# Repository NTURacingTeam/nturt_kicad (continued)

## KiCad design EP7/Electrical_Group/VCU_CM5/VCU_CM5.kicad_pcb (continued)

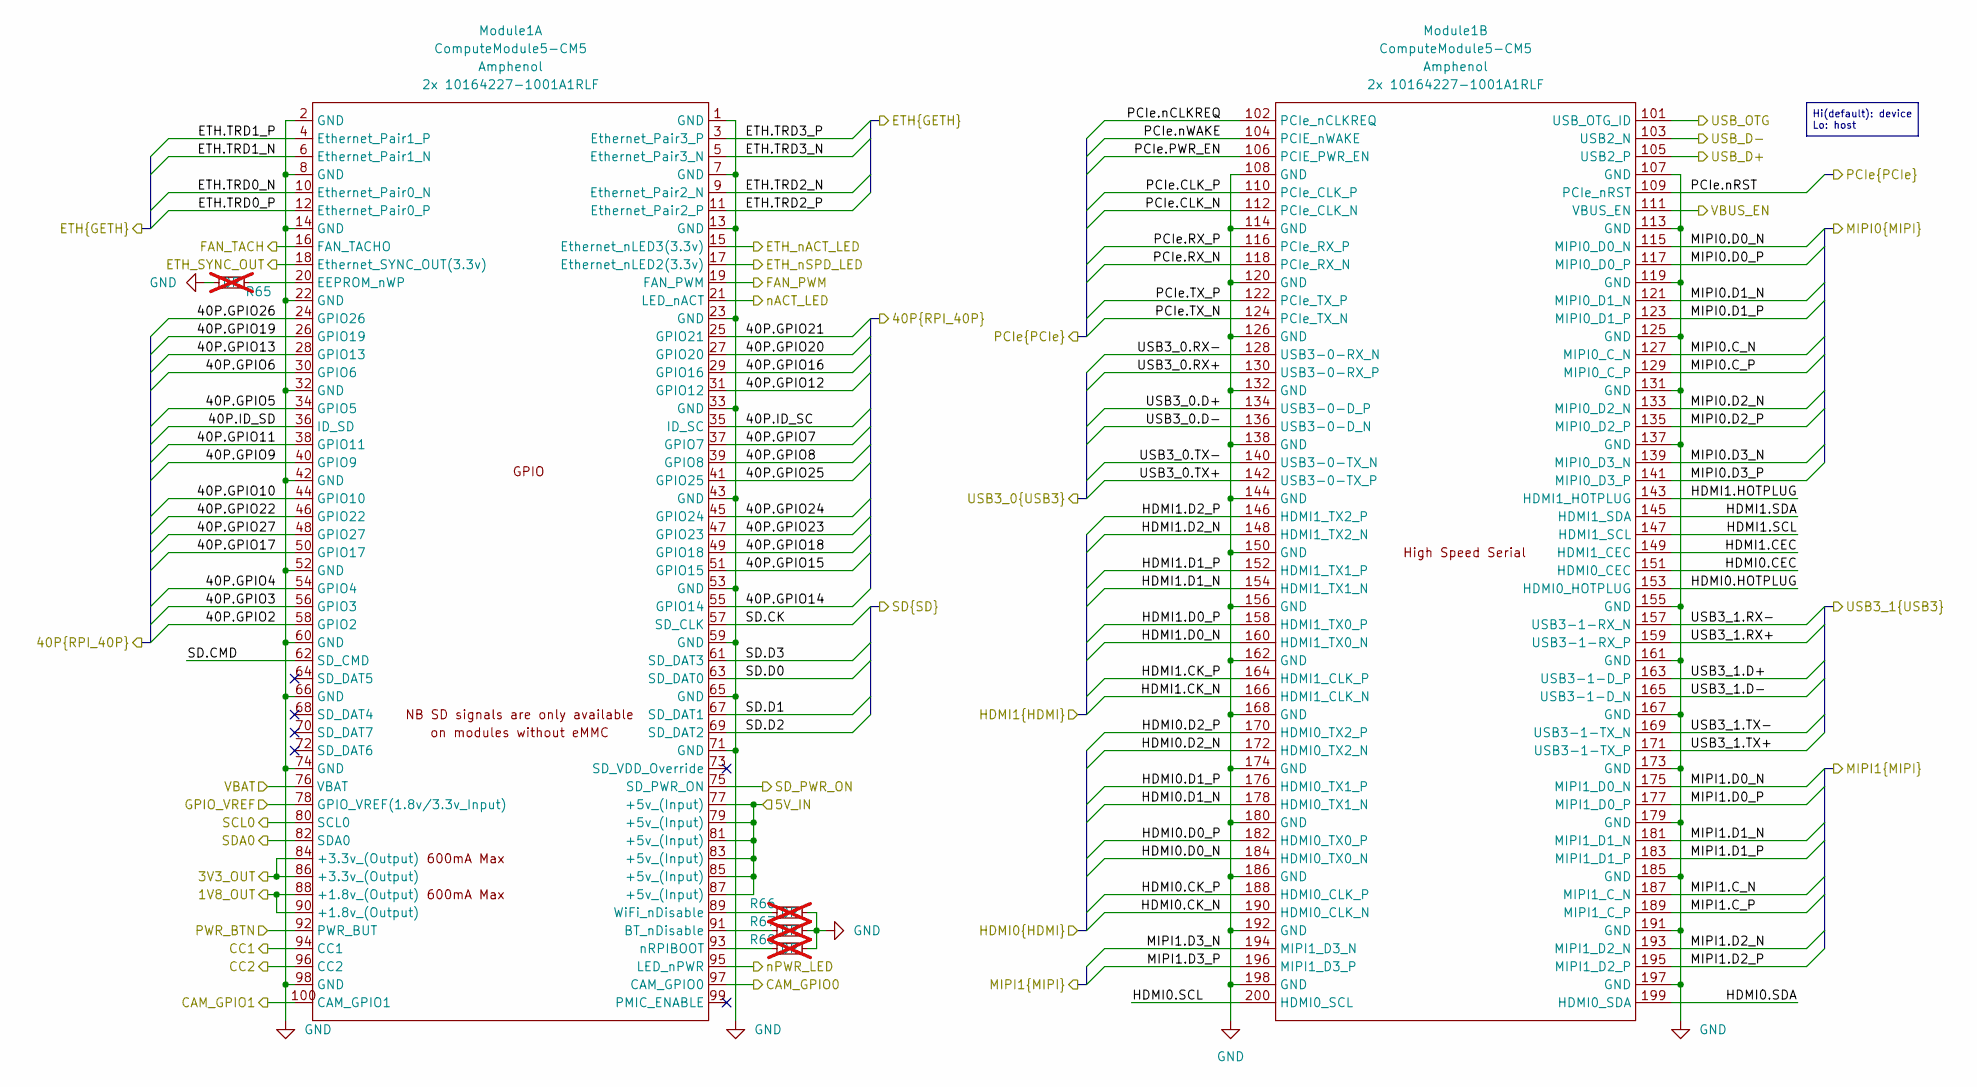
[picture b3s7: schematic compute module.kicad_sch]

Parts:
Module1: ComputeModule5-CM5; Raspberry-Pi-5-Compute-Module
R65, R66, R67, R68: 0R; R_0402_1005Metric; not fitted

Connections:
+1V8_CMOUT: Module1.88 (+1.8v_(Output)), Module1.90 (+1.8v_(Output))
+3V3_CMOUT: Module1.78 (GPIO_VREF(1.8v/3.3v_Input)), Module1.84 (+3.3v_(Output)), Module1.86 (+3.3v_(Output)); also elsewhere on the board
+3V_BAT: Module1.76 (VBAT); also elsewhere on the board
+5V_CM: Module1.77 (+5v_(Input)), Module1.79 (+5v_(Input)), Module1.81 (+5v_(Input)), Module1.83 (+5v_(Input)), Module1.85 (+5v_(Input)), Module1.87 (+5v_(Input))
/USB3_1.D+: Module1.163 (USB3-1-D_P); also elsewhere on the board
/USB3_1.D-: Module1.165 (USB3-1-D_N); also elsewhere on the board
/USB3_1.RX+: Module1.159 (USB3-1-RX_P); also elsewhere on the board
/USB3_1.RX-: Module1.157 (USB3-1-RX_N); also elsewhere on the board
/USB3_1.TX+: Module1.171 (USB3-1-TX_P); also elsewhere on the board
/USB3_1.TX-: Module1.169 (USB3-1-TX_N); also elsewhere on the board
/computer/40P.GPIO2: Module1.58 (GPIO2)
/computer/40P.GPIO3: Module1.56 (GPIO3)
/computer/40P.GPIO4: Module1.54 (GPIO4)
/computer/40P.GPIO5: Module1.34 (GPIO5)
/computer/40P.GPIO6: Module1.30 (GPIO6)
/computer/40P.GPIO7: Module1.37 (GPIO7)
/computer/40P.GPIO8: Module1.39 (GPIO8)
/computer/40P.GPIO9: Module1.40 (GPIO9)
/computer/40P.GPIO10: Module1.44 (GPIO10)
/computer/40P.GPIO11: Module1.38 (GPIO11)
/computer/40P.GPIO12: Module1.31 (GPIO12)
/computer/40P.GPIO13: Module1.28 (GPIO13); also elsewhere on the board
/computer/40P.GPIO14: Module1.55 (GPIO14)
/computer/40P.GPIO15: Module1.51 (GPIO15)
/computer/40P.GPIO16: Module1.29 (GPIO16)
/computer/40P.GPIO17: Module1.50 (GPIO17); also elsewhere on the board
/computer/40P.GPIO18: Module1.49 (GPIO18); also elsewhere on the board
/computer/40P.GPIO19: Module1.26 (GPIO19); also elsewhere on the board
/computer/40P.GPIO20: Module1.27 (GPIO20); also elsewhere on the board
/computer/40P.GPIO21: Module1.25 (GPIO21); also elsewhere on the board
/computer/40P.GPIO22: Module1.46 (GPIO22); also elsewhere on the board
/computer/40P.GPIO23: Module1.47 (GPIO23)
/computer/40P.GPIO24: Module1.45 (GPIO24)
/computer/40P.GPIO25: Module1.41 (GPIO25)
/computer/40P.GPIO26: Module1.24 (GPIO26)
/computer/40P.GPIO27: Module1.48 (GPIO27)
/computer/40P.ID_SC: Module1.35 (ID_SC); also elsewhere on the board
/computer/40P.ID_SD: Module1.36 (ID_SD); also elsewhere on the board
/computer/MIPI0.C_N: Module1.127 (MIPI0_C_N); also elsewhere on the board
/computer/MIPI0.C_P: Module1.129 (MIPI0_C_P); also elsewhere on the board
/computer/MIPI0.D0_N: Module1.115 (MIPI0_D0_N); also elsewhere on the board
/computer/MIPI0.D0_P: Module1.117 (MIPI0_D0_P); also elsewhere on the board
/computer/MIPI0.D1_N: Module1.121 (MIPI0_D1_N); also elsewhere on the board
/computer/MIPI0.D1_P: Module1.123 (MIPI0_D1_P); also elsewhere on the board
/computer/MIPI0.D2_N: Module1.133 (MIPI0_D2_N); also elsewhere on the board
/computer/MIPI0.D2_P: Module1.135 (MIPI0_D2_P); also elsewhere on the board
/computer/MIPI0.D3_N: Module1.139 (MIPI0_D3_N); also elsewhere on the board
/computer/MIPI0.D3_P: Module1.141 (MIPI0_D3_P); also elsewhere on the board
/computer/MIPI0.GPIO0: Module1.97 (CAM_GPIO0); also elsewhere on the board
/computer/MIPI0.GPIO1: Module1.100 (CAM_GPIO1); also elsewhere on the board
/computer/MIPI0.SCL: Module1.80 (SCL0); also elsewhere on the board
/computer/MIPI0.SDA: Module1.82 (SDA0); also elsewhere on the board
/computer/PCIe.CLK_N: Module1.112 (PCIe_CLK_N)
/computer/PCIe.CLK_P: Module1.110 (PCIe_CLK_P)
/computer/PCIe.PWR_EN: Module1.106 (PCIE_PWR_EN)
/computer/PCIe.RX_N: Module1.118 (PCIe_RX_N)
/computer/PCIe.RX_P: Module1.116 (PCIe_RX_P)
/computer/PCIe.TX_N: Module1.124 (PCIe_TX_N)
/computer/PCIe.TX_P: Module1.122 (PCIe_TX_P)
/computer/PCIe.nCLKREQ: Module1.102 (PCIe_nCLKREQ)
/computer/PCIe.nRST: Module1.109 (PCIe_nRST)
/computer/PCIe.nWAKE: Module1.104 (PCIE_nWAKE)
/computer/SD.CK: Module1.57 (SD_CLK); also elsewhere on the board
/computer/SD.CMD: Module1.62 (SD_CMD); also elsewhere on the board
/computer/SD.D0: Module1.63 (SD_DAT0); also elsewhere on the board
/computer/SD.D1: Module1.67 (SD_DAT1); also elsewhere on the board
/computer/SD.D2: Module1.69 (SD_DAT2); also elsewhere on the board
/computer/SD.D3: Module1.61 (SD_DAT3); also elsewhere on the board
/computer/SD_PWR_ON: Module1.75 (SD_PWR_ON); also elsewhere on the board
/computer/USB3_0.D+: Module1.134 (USB3-0-D_P); also elsewhere on the board
/computer/USB3_0.D-: Module1.136 (USB3-0-D_N); also elsewhere on the board
/computer/USB3_0.RX+: Module1.130 (USB3-0-RX_P)
/computer/USB3_0.RX-: Module1.128 (USB3-0-RX_N)
/computer/USB3_0.TX+: Module1.142 (USB3-0-TX_P)
/computer/USB3_0.TX-: Module1.140 (USB3-0-TX_N)
/computer/compute module/CC1: Module1.94 (CC1)
/computer/compute module/CC2: Module1.96 (CC2)
/computer/compute module/ETH.TRD0_N: Module1.10 (Ethernet_Pair0_N)
/computer/compute module/ETH.TRD0_P: Module1.12 (Ethernet_Pair0_P)
/computer/compute module/ETH.TRD1_N: Module1.6 (Ethernet_Pair1_N)
/computer/compute module/ETH.TRD1_P: Module1.4 (Ethernet_Pair1_P)
/computer/compute module/ETH.TRD2_N: Module1.9 (Ethernet_Pair2_N)
/computer/compute module/ETH.TRD2_P: Module1.11 (Ethernet_Pair2_P)
/computer/compute module/ETH.TRD3_N: Module1.5 (Ethernet_Pair3_N)
/computer/compute module/ETH.TRD3_P: Module1.3 (Ethernet_Pair3_P)
/computer/compute module/ETH_SYNC_OUT: Module1.18 (Ethernet_SYNC_OUT(3.3v))
/computer/compute module/ETH_nACT_LED: Module1.15 (Ethernet_nLED3(3.3v))
/computer/compute module/ETH_nSPD_LED: Module1.17 (Ethernet_nLED2(3.3v))
/computer/compute module/FAN_PWM: Module1.19 (FAN_PWM); also elsewhere on the board
/computer/compute module/FAN_TACH: Module1.16 (FAN_TACHO); also elsewhere on the board
/computer/compute module/HDMI0.CEC: Module1.151 (HDMI0_CEC)
/computer/compute module/HDMI0.CK_N: Module1.190 (HDMI0_CLK_N)
/computer/compute module/HDMI0.CK_P: Module1.188 (HDMI0_CLK_P)
/computer/compute module/HDMI0.D0_N: Module1.184 (HDMI0_TX0_N)
/computer/compute module/HDMI0.D0_P: Module1.182 (HDMI0_TX0_P)
/computer/compute module/HDMI0.D1_N: Module1.178 (HDMI0_TX1_N)
/computer/compute module/HDMI0.D1_P: Module1.176 (HDMI0_TX1_P)
/computer/compute module/HDMI0.D2_N: Module1.172 (HDMI0_TX2_N)
/computer/compute module/HDMI0.D2_P: Module1.170 (HDMI0_TX2_P)
/computer/compute module/HDMI0.HOTPLUG: Module1.153 (HDMI0_HOTPLUG)
/computer/compute module/HDMI0.SCL: Module1.200 (HDMI0_SCL)
/computer/compute module/HDMI0.SDA: Module1.199 (HDMI0_SDA)
/computer/compute module/HDMI1.CEC: Module1.149 (HDMI1_CEC)
/computer/compute module/HDMI1.CK_N: Module1.166 (HDMI1_CLK_N)
/computer/compute module/HDMI1.CK_P: Module1.164 (HDMI1_CLK_P)
/computer/compute module/HDMI1.D0_N: Module1.160 (HDMI1_TX0_N)
/computer/compute module/HDMI1.D0_P: Module1.158 (HDMI1_TX0_P)
/computer/compute module/HDMI1.D1_N: Module1.154 (HDMI1_TX1_N)
/computer/compute module/HDMI1.D1_P: Module1.152 (HDMI1_TX1_P)
/computer/compute module/HDMI1.D2_N: Module1.148 (HDMI1_TX2_N)
/computer/compute module/HDMI1.D2_P: Module1.146 (HDMI1_TX2_P)
/computer/compute module/HDMI1.HOTPLUG: Module1.143 (HDMI1_HOTPLUG)
/computer/compute module/HDMI1.SCL: Module1.147 (HDMI1_SCL)
/computer/compute module/HDMI1.SDA: Module1.145 (HDMI1_SDA)
/computer/compute module/MIPI1.C_N: Module1.187 (MIPI1_C_N); also elsewhere on the board
/computer/compute module/MIPI1.C_P: Module1.189 (MIPI1_C_P); also elsewhere on the board
/computer/compute module/MIPI1.D0_N: Module1.175 (MIPI1_D0_N); also elsewhere on the board
/computer/compute module/MIPI1.D0_P: Module1.177 (MIPI1_D0_P); also elsewhere on the board
/computer/compute module/MIPI1.D1_N: Module1.181 (MIPI1_D1_N); also elsewhere on the board
/computer/compute module/MIPI1.D1_P: Module1.183 (MIPI1_D1_P); also elsewhere on the board
/computer/compute module/MIPI1.D2_N: Module1.193 (MIPI1_D2_N)
/computer/compute module/MIPI1.D2_P: Module1.195 (MIPI1_D2_P)
/computer/compute module/MIPI1.D3_N: Module1.194 (MIPI1_D3_N)
/computer/compute module/MIPI1.D3_P: Module1.196 (MIPI1_D3_P)
/computer/compute module/PWR_BTN: Module1.92 (PWR_BUT); also elsewhere on the board
/computer/compute module/USB_D+: Module1.105 (USB2_P)
/computer/compute module/USB_D-: Module1.103 (USB2_N)
/computer/compute module/VBUS_EN: Module1.111 (VBUS_EN)
/computer/compute module/nACT_LED: Module1.21 (LED_nACT); also elsewhere on the board
/computer/compute module/nPWR_LED: Module1.95 (LED_nPWR)
GND: Module1.1 (GND), Module1.2 (GND), Module1.7 (GND), Module1.8 (GND), Module1.13 (GND), Module1.14 (GND), Module1.22 (GND), Module1.23 (GND), Module1.32 (GND), Module1.33 (GND), Module1.42 (GND), Module1.43 (GND), Module1.52 (GND), Module1.53 (GND), Module1.59 (GND), Module1.60 (GND), Module1.65 (GND), Module1.66 (GND), Module1.71 (GND), Module1.74 (GND), Module1.98 (GND), Module1.101 (USB_OTG_ID), Module1.107 (GND), Module1.108 (GND), Module1.113 (GND), Module1.114 (GND), Module1.119 (GND), Module1.120 (GND), Module1.125 (GND), Module1.126 (GND), Module1.131 (GND), Module1.132 (GND), Module1.137 (GND), Module1.138 (GND), Module1.144 (GND), Module1.150 (GND), Module1.155 (GND), Module1.156 (GND), Module1.161 (GND), Module1.162 (GND), Module1.167 (GND), Module1.168 (GND), Module1.173 (GND), Module1.174 (GND), Module1.179 (GND), Module1.180 (GND), Module1.185 (GND), Module1.186 (GND), Module1.191 (GND), Module1.192 (GND), Module1.197 (GND), Module1.198 (GND), R65.1, R66.2, R67.2, R68.2; also elsewhere on the board
unnamed: Module1.91 (BT_nDisable), R67.1
unnamed: Module1.20 (EEPROM_nWP), R65.2
unnamed: Module1.89 (WiFi_nDisable), R66.1
unnamed: Module1.93 (nRPIBOOT), R68.1

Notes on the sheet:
Hi(default): device Lo: host

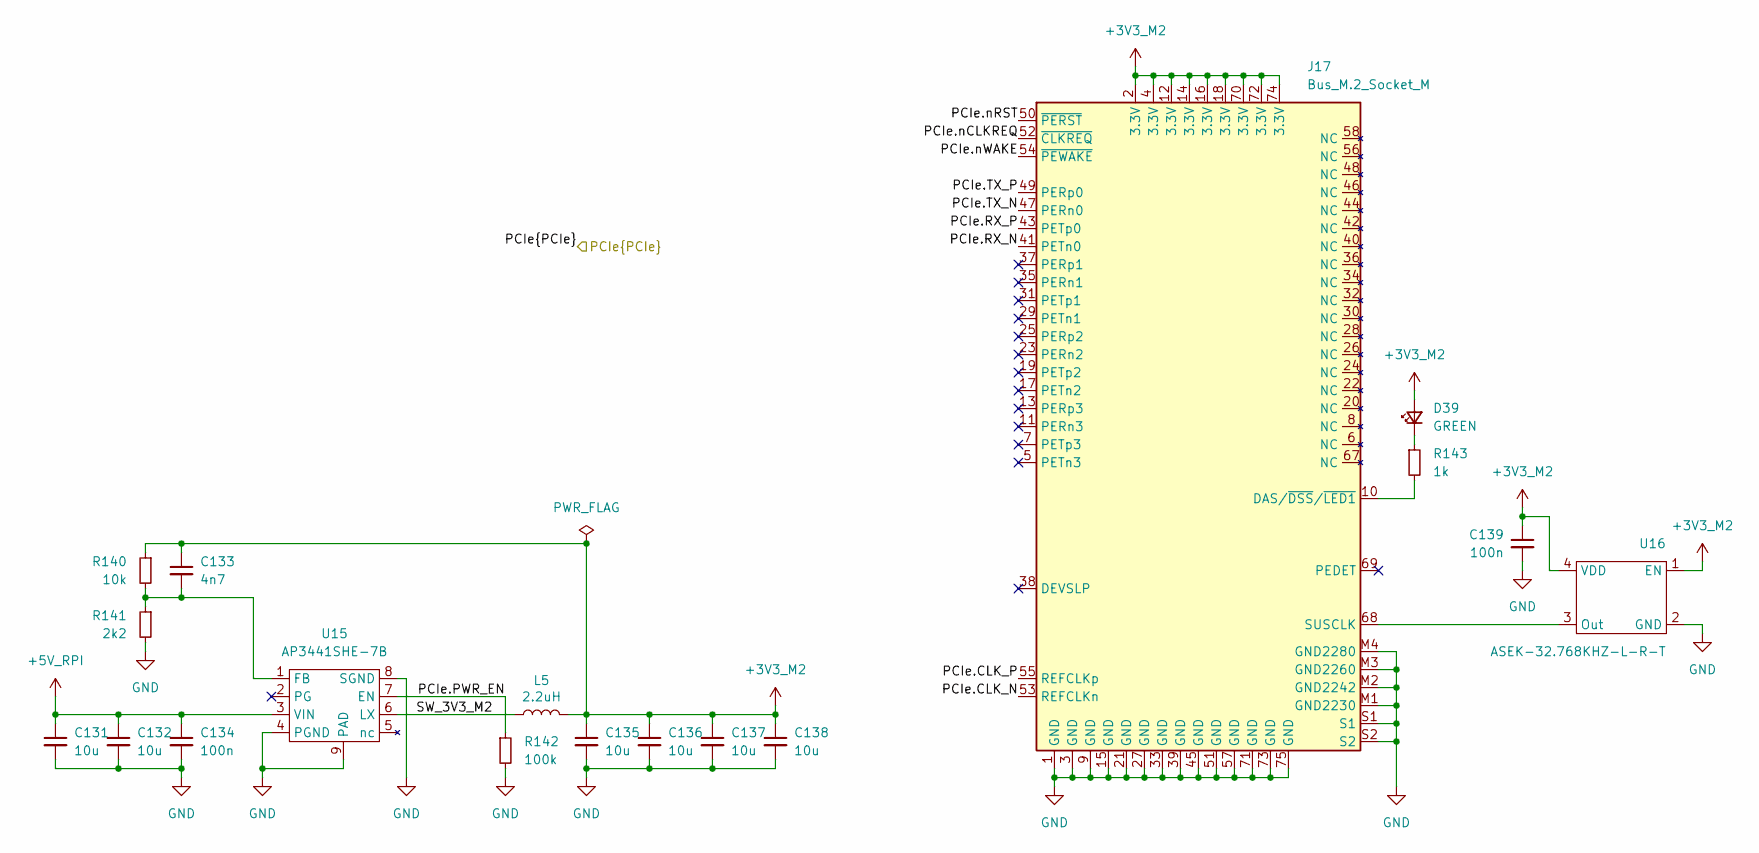
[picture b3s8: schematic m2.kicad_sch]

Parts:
C131, C132, C135, C136, C137, C138: 10u; C_0603_1608Metric
C133: 4n7; C_0402_1005Metric
C134, C139: 100n; C_0402_1005Metric
D39: GREEN; LED_0603_1608Metric
J17: Bus_M.2_Socket_M; M.2 M Key socket; Part Description M.2 M Key connector
L5: 2.2uH; L_Bourns_SRP5030CC; Part Description Inductor, SMT, 2520, 2u2, IRMS=7A, ISAT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
R140: 10k; R_0402_1005Metric
R141: 2k2; R_0402_1005Metric
R142: 100k; R_0402_1005Metric
R143: 1k; R_0402_1005Metric
U15: AP3441SHE-7B; DFN-8-1EP_2x2mm_P0.5mm_EP1.05x1.75mm
U16: ASEK-32.768KHZ-L-R-T; Crystal_SMD_3225-4Pin_3.2x2.5mm; Part Description 32KHz Xtal oscilator

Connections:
unnamed: C131.1, C132.1, C134.1, U15.3 (VIN)
unnamed: C131.2, C132.2, C134.2, C135.2, C136.2, C137.2, C138.2, C139.2, J17.1 (GND), J17.3 (GND), J17.9 (GND), J17.15 (GND), J17.21 (GND), J17.27 (GND), J17.33 (GND), J17.39 (GND), J17.45 (GND), J17.51 (GND), J17.57 (GND), J17.71 (GND), J17.73 (GND), J17.75 (GND), J17.M1 (GND2230), J17.M2 (GND2242), J17.M3 (GND2260), J17.M4 (GND2280), J17.S1, J17.S2, R141.2, R142.2, U15.4 (PGND), U15.8 (SGND), U15.9 (PAD), U16.2 (GND)
unnamed: C133.1, C135.1, C136.1, C137.1, C138.1, C139.1, D39.2 (A), J17.2 (3.3V), J17.4 (3.3V), J17.12 (3.3V), J17.14 (3.3V), J17.16 (3.3V), J17.18 (3.3V), J17.70 (3.3V), J17.72 (3.3V), J17.74 (3.3V), L5.2, R140.1, U16.1 (EN), U16.4 (VDD)
unnamed: C133.2, R140.2, R141.1, U15.1 (FB)
unnamed: D39.1 (K), R143.1
unnamed: J17.10 (DAS/~DSS/~LED1), R143.2
unnamed: J17.68 (SUSCLK), U16.3 (Out)
unnamed: L5.1, U15.6 (LX)
unnamed: R142.1, U15.7 (EN)

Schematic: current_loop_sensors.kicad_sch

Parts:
J11: Conn_01x30_Socket; Amphenol_F32Q-1A7x1-11030_1x30-1MP_P0.5mm_Horizontal
R69, R70, R71, R72, R73, R74, R75, R76, R77, R78, R79, R80, R81, R82, R83: 10R; R_0603_1608Metric

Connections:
+24V: R69.2, R70.2, R71.2, R72.2, R73.2, R74.2, R75.2, R76.2, R77.2, R78.2, R79.2, R80.2, R81.2, R82.2, R83.2; also elsewhere on the board
/vcu mcu/current loop sensors/CL_CH1: J11.2; also elsewhere on the board
/vcu mcu/current loop sensors/CL_CH2: J11.4; also elsewhere on the board
/vcu mcu/current loop sensors/CL_CH3: J11.6; also elsewhere on the board
/vcu mcu/current loop sensors/CL_CH4: J11.8; also elsewhere on the board
/vcu mcu/current loop sensors/CL_CH5: J11.10; also elsewhere on the board
/vcu mcu/current loop sensors/CL_CH6: J11.12; also elsewhere on the board
/vcu mcu/current loop sensors/CL_CH7: J11.14; also elsewhere on the board
/vcu mcu/current loop sensors/CL_CH8: J11.16; also elsewhere on the board
/vcu mcu/current loop sensors/CL_CH9: J11.18; also elsewhere on the board
/vcu mcu/current loop sensors/CL_CH10: J11.20; also elsewhere on the board
/vcu mcu/current loop sensors/CL_CH11: J11.22; also elsewhere on the board
/vcu mcu/current loop sensors/CL_CH12: J11.24; also elsewhere on the board
/vcu mcu/current loop sensors/CL_CH13: J11.26; also elsewhere on the board
/vcu mcu/current loop sensors/CL_CH14: J11.28; also elsewhere on the board
/vcu mcu/current loop sensors/CL_CH15: J11.30; also elsewhere on the board
unnamed: J11.1, R69.1
unnamed: J11.3, R70.1
unnamed: J11.5, R71.1
unnamed: J11.7, R72.1
unnamed: J11.9, R73.1
unnamed: J11.11, R74.1
unnamed: J11.13, R75.1
unnamed: J11.15, R76.1
unnamed: J11.17, R77.1
unnamed: J11.19, R78.1
unnamed: J11.21, R79.1
unnamed: J11.23, R80.1
unnamed: J11.25, R81.1
unnamed: J11.27, R82.1
unnamed: J11.29, R83.1

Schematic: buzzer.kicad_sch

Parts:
D35: WHITE LED; LED_0603_1608Metric
J15: buzzer; JST_XH_B2B-XH-A_1x02_P2.50mm_Vertical
Q4: 2N7002; SOT-23
R129: 100; R_0402_1005Metric
R130: 100k; R_0402_1005Metric
R131: 10k; R_0402_1005Metric

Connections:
+24V: D35.2 (A), J15.2; also elsewhere on the board
/vcu mcu/buzzer/buzzer_outbox: J15.1, Q4.3 (D), R131.1
/vcu mcu/buzzer/buzzer_s: R129.2
GND: Q4.2 (S), R130.1; also elsewhere on the board
unnamed: D35.1 (K), R131.2
unnamed: Q4.1 (G), R129.1, R130.2

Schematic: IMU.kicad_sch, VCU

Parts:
C24, C25: 0u1; C_0402_1005Metric
R13: 0R; R_0402_1005Metric
R14: 10k; R_0402_1005Metric
R15, R16: 3k3; R_0402_1005Metric
U4: LSM6DSOX; LGA-14_3x2.5mm_P0.5mm_LayoutBorder3x4y; Mouser Part Number 511-LSM6DSOXTR

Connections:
+3V3: C24.2, C25.2, R13.2, R15.1, R16.1, U4.5 (VDDIO), U4.8 (VDD), U4.12 (CS); also elsewhere on the board
/vcu mcu/I2C4_SCL: R15.2, U4.13 (SCL); also elsewhere on the board
/vcu mcu/I2C4_SDA: R16.2, U4.14 (SDA); also elsewhere on the board
/vcu mcu/IMU/LSM6D_INT1: U4.4 (INT1)
/vcu mcu/IMU/LSM6D_INT2: U4.9 (INT2)
GND: C24.1, C25.1, R14.1, U4.2 (SDX), U4.3 (SCX), U4.6 (GND_1), U4.7 (GND_2); also elsewhere on the board
unnamed: R13.1, R14.2, U4.1 (SDO/SA0)

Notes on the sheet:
adress: 1101011b or 1101010b depend on SDO/SAO
only use I2C mode

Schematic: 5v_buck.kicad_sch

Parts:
C12, C13: 10u 50V; C_1206_3216Metric
C14: 0u1; C_0603_1608Metric
C15: 10n; C_0603_1608Metric
C16, C17, C18, C19, C20, C21: 47u 10V; C_1206_3216Metric
D2: SS54; D_SMA
D3: SMBJ5.0A; D_SMB
F2: 3A; Fuse_1206_3216Metric
L3: 22uH 3.7A (SMDRI129-220MT); L_Bourns_SRR1260
R8: 47k 1%; R_0402_1005Metric
R9: 15k 1%; R_0402_1005Metric
U2: TPS5430DDA; TI_SO-PowerPAD-8_ThermalVias

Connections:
+5V_RPI: D3.1 (K), F2.2; also elsewhere on the board
/power/5v buck mcu/24V_IN: C12.1, C13.1, C14.2, U2.7 (VIN); also elsewhere on the board
GND: C12.2, C13.2, C14.1, C16.2, C17.2, C18.2, C19.2, C20.2, C21.2, D2.2 (A), D3.2 (A), R9.2, U2.6 (GND), U2.9 (GNDPAD); also elsewhere on the board
unnamed: C16.1, C17.1, C18.1, C19.1, C20.1, C21.1, F2.1, L3.2, R8.1
unnamed: C15.2, D2.1 (K), L3.1, U2.8 (PH)
unnamed: C15.1, U2.1 (BOOT)
unnamed: R8.2, R9.1, U2.4 (VSENSE)

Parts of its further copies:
C109, C110: 10u 50V; C_1206_3216Metric
C111: 0u1; C_0603_1608Metric
C112: 10n; C_0603_1608Metric
C113, C114, C115, C116, C117, C118: 47u 10V; C_1206_3216Metric
D36: SS54; D_SMA
D37: SMBJ5.0A; D_SMB
F3: 3A; Fuse_1206_3216Metric
L4: 22uH 3.7A (SMDRI129-220MT); L_Bourns_SRR1260
R132: 47k 1%; R_0402_1005Metric
R133: 15k 1%; R_0402_1005Metric
U12: TPS5430DDA; TI_SO-PowerPAD-8_ThermalVias

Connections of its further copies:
+5V: D37.1 (K), F3.2; also elsewhere on the board
/power/5v buck mcu/24V_IN: C109.1, C110.1, C111.2, U12.7 (VIN); also elsewhere on the board
GND: C109.2, C110.2, C111.1, C113.2, C114.2, C115.2, C116.2, C117.2, C118.2, D36.2 (A), D37.2 (A), R133.2, U12.6 (GND), U12.9 (GNDPAD); also elsewhere on the board
unnamed: C113.1, C114.1, C115.1, C116.1, C117.1, C118.1, F3.1, L4.2, R132.1
unnamed: C112.2, D36.1 (K), L4.1, U12.8 (PH)
unnamed: C112.1, U12.1 (BOOT)
unnamed: R132.2, R133.1, U12.4 (VSENSE)

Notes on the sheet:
FB Vref=1.221 R_FBB = 10k ~ 100k possible R_FBT, R_FBB 16,5.1 => 5.05 V 18, 5.6 => 5.146 V 7.5, 2.4 => 5.037 V 5.1, 1.6 => 5.113 V

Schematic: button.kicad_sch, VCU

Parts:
C26: 330p; C_0402_1005Metric
D5: WHITE Button; LED_0603_1608Metric
R17: 1k; R_0402_1005Metric
R18, R19: 10k; R_0402_1005Metric

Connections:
+3V3: D5.2 (A), R18.2; also elsewhere on the board
/vcu mcu/button3: C26.1, R19.1; also elsewhere on the board
/vcu mcu/button_raw3: R17.2, R18.1, R19.2
GND: C26.2; also elsewhere on the board
unnamed: D5.1 (K), R17.1

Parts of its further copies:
C27, C28, C29, C30, C31, C32: 330p; C_0402_1005Metric
D6, D7, D8, D9, D10, D11: WHITE Button; LED_0603_1608Metric
R20, R23, R26, R29, R32, R35: 1k; R_0402_1005Metric
R21, R22, R24, R25, R27, R28, R30, R31, R33, R34, R36, R37: 10k; R_0402_1005Metric

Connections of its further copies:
+3V3: D6.2 (A), D7.2 (A), D8.2 (A), D9.2 (A), D10.2 (A), D11.2 (A), R21.2, R24.2, R27.2, R30.2, R33.2, R36.2; also elsewhere on the board
/vcu mcu/button1: C27.1, R22.1; also elsewhere on the board
/vcu mcu/button2: C28.1, R25.1; also elsewhere on the board
/vcu mcu/button4: C30.1, R31.1; also elsewhere on the board
/vcu mcu/button5: C29.1, R28.1; also elsewhere on the board
/vcu mcu/button6: C32.1, R37.1; also elsewhere on the board
/vcu mcu/button7: C31.1, R34.1; also elsewhere on the board
/vcu mcu/button_raw1: R20.2, R21.1, R22.2; also elsewhere on the board
/vcu mcu/button_raw2: R23.2, R24.1, R25.2
/vcu mcu/button_raw4: R29.2, R30.1, R31.2
/vcu mcu/button_raw5: R26.2, R27.1, R28.2
/vcu mcu/button_raw6: R35.2, R36.1, R37.2
/vcu mcu/button_raw7: R32.2, R33.1, R34.2
GND: C27.2, C28.2, C29.2, C30.2, C31.2, C32.2; also elsewhere on the board
unnamed: D6.1 (K), R20.1
unnamed: D7.1 (K), R23.1
unnamed: D8.1 (K), R26.1
unnamed: D9.1 (K), R29.1
unnamed: D10.1 (K), R32.1
unnamed: D11.1 (K), R35.1

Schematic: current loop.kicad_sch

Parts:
C33: 1n; C_0402_1005Metric
C34: 10u; C_0402_1005Metric
D12: zener 3.6V; D_SOD-523
R38: 150R 1%; R_0603_1608Metric

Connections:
/vcu mcu/current loop sensors/CL_CH1: C33.1, C34.1, D12.1 (K), R38.1; also elsewhere on the board
GND: C33.2, C34.2, D12.2 (A), R38.2; also elsewhere on the board

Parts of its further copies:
C56, C58, C60, C62, C64, C66, C68, C70, C72, C74, C76, C78, C80, C107: 1n; C_0402_1005Metric
C57, C59, C61, C63, C65, C67, C69, C71, C73, C75, C77, C79, C81, C108: 10u; C_0402_1005Metric
D16, D17, D18, D19, D20, D21, D22, D23, D24, D25, D26, D27, D28, D34: zener 3.6V; D_SOD-523
R84, R85, R86, R87, R88, R89, R90, R91, R92, R93, R94, R95, R96, R128: 150R 1%; R_0603_1608Metric

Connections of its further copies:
/vcu mcu/current loop sensors/CL_CH2: C56.1, C57.1, D16.1 (K), R84.1; also elsewhere on the board
/vcu mcu/current loop sensors/CL_CH3: C58.1, C59.1, D17.1 (K), R85.1; also elsewhere on the board
/vcu mcu/current loop sensors/CL_CH4: C60.1, C61.1, D18.1 (K), R86.1; also elsewhere on the board
/vcu mcu/current loop sensors/CL_CH5: C62.1, C63.1, D19.1 (K), R87.1; also elsewhere on the board
/vcu mcu/current loop sensors/CL_CH6: C64.1, C65.1, D20.1 (K), R88.1; also elsewhere on the board
/vcu mcu/current loop sensors/CL_CH7: C66.1, C67.1, D21.1 (K), R89.1; also elsewhere on the board
/vcu mcu/current loop sensors/CL_CH8: C68.1, C69.1, D22.1 (K), R90.1; also elsewhere on the board
/vcu mcu/current loop sensors/CL_CH9: C70.1, C71.1, D23.1 (K), R91.1; also elsewhere on the board
/vcu mcu/current loop sensors/CL_CH10: C72.1, C73.1, D24.1 (K), R92.1; also elsewhere on the board
/vcu mcu/current loop sensors/CL_CH11: C74.1, C75.1, D25.1 (K), R93.1; also elsewhere on the board
/vcu mcu/current loop sensors/CL_CH12: C76.1, C77.1, D26.1 (K), R94.1; also elsewhere on the board
/vcu mcu/current loop sensors/CL_CH13: C78.1, C79.1, D27.1 (K), R95.1; also elsewhere on the board
/vcu mcu/current loop sensors/CL_CH14: C80.1, C81.1, D28.1 (K), R96.1; also elsewhere on the board
/vcu mcu/current loop sensors/CL_CH15: C107.1, C108.1, D34.1 (K), R128.1; also elsewhere on the board
GND: C56.2, C57.2, C58.2, C59.2, C60.2, C61.2, C62.2, C63.2, C64.2, C65.2, C66.2, C67.2, C68.2, C69.2, C70.2, C71.2, C72.2, C73.2, C74.2, C75.2, C76.2, C77.2, C78.2, C79.2, C80.2, C81.2, C107.2, C108.2, D16.2 (A), D17.2 (A), D18.2 (A), D19.2 (A), D20.2 (A), D21.2 (A), D22.2 (A), D23.2 (A), D24.2 (A), D25.2 (A), D26.2 (A), D27.2 (A), D28.2 (A), D34.2 (A), R84.2, R85.2, R86.2, R87.2, R88.2, R89.2, R90.2, R91.2, R92.2, R93.2, R94.2, R95.2, R96.2, R128.2; also elsewhere on the board

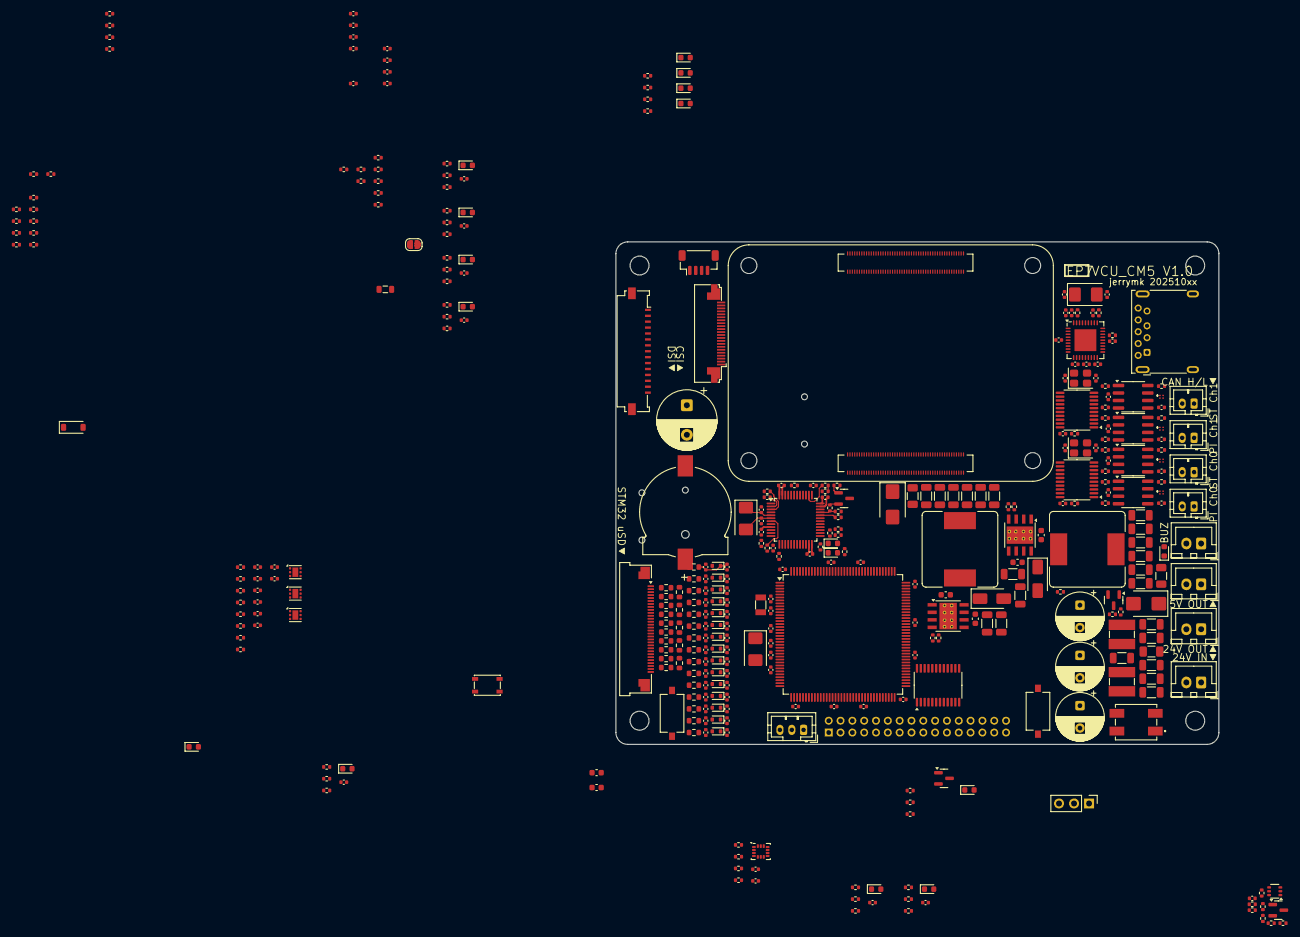
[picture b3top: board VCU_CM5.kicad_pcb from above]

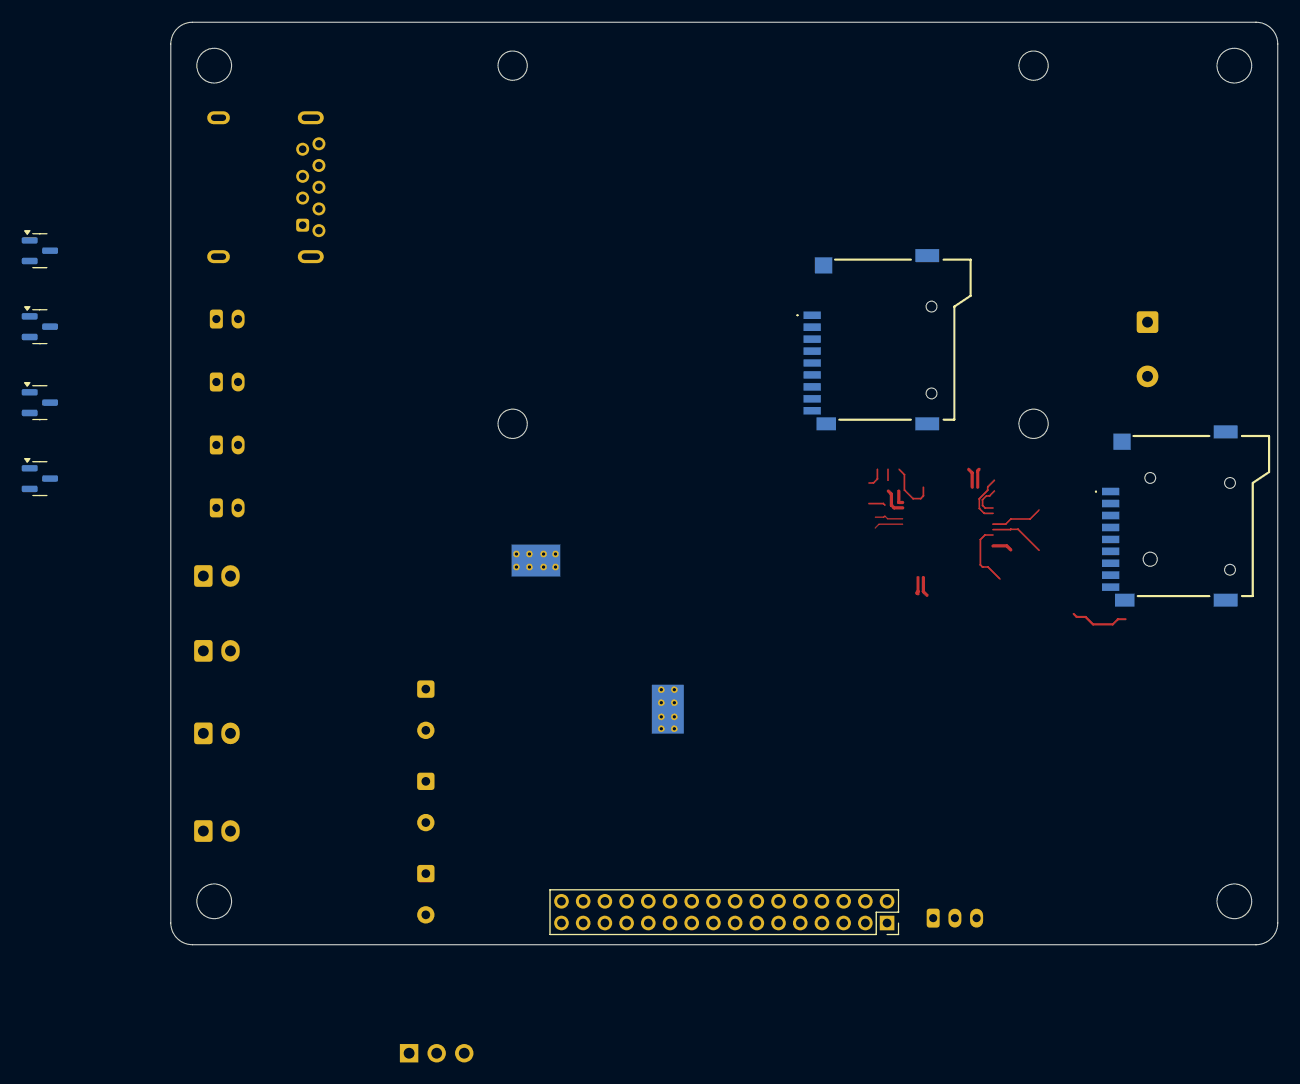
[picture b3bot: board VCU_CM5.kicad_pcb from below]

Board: 6 copper layers, 102.0 x 85.0 mm, 386 parts (7 on the bottom side), 268 nets.

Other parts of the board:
C22, C23, C119, C120, C140, C141, C142, C143: 0u1; C_0402_1005Metric
D4, D38, D40, D41: NUP2105L; SOT-23
FL2, FL3, FL4, FL5: EXC14CE121U; EXCX4CE900U
J5, J16, J18, J19: CAN; JST_PH_B2B-PH-K_1x02_P2.00mm_Vertical
R10, R11, R134, R135, R144, R145, R147, R148: 22R; R_0402_1005Metric
R12, R136, R146, R149: 10k; R_0402_1005Metric
U3, U13, U17, U18: TCAN1042VDRQ1; SOIC-8_3.9x4.9mm_P1.27mm

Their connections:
+3V3: C23.1, C120.1, C141.1, C143.1, U3.5 (VIO), U13.5 (VIO), U17.5 (VIO), U18.5 (VIO); also elsewhere on the board
+5V: C22.1, C119.1, C140.1, C142.1, U3.3 (VCC), U13.3 (VCC), U17.3 (VCC), U18.3 (VCC); also elsewhere on the board
/CAN 1/CAN+: D40.1 (K), FL4.4, J18.2
/CAN 1/CAN-: D40.2 (K), FL4.3, J18.1
/CAN 1/CAN.RX: R145.1; also elsewhere on the board
/CAN 1/CAN.TX: R144.1; also elsewhere on the board
/CAN 2/CAN+: D38.1 (K), FL3.4, J16.2
/CAN 2/CAN-: D38.2 (K), FL3.3, J16.1
/CAN 2/CAN.RX: R135.1; also elsewhere on the board
/CAN 2/CAN.TX: R134.1; also elsewhere on the board
/CAN 3/CAN+: D41.1 (K), FL5.4, J19.2
/CAN 3/CAN-: D41.2 (K), FL5.3, J19.1
/CAN 3/CAN.RX: R148.1; also elsewhere on the board
/CAN 3/CAN.TX: R147.1; also elsewhere on the board
/CAN 4/CAN+: D4.1 (K), FL2.4, J5.2
/CAN 4/CAN-: D4.2 (K), FL2.3, J5.1
/CAN 4/CAN.RX: R11.1; also elsewhere on the board
/CAN 4/CAN.TX: R10.1; also elsewhere on the board
GND: C22.2, C23.2, C119.2, C120.2, C140.2, C141.2, C142.2, C143.2, D4.3 (A), D38.3 (A), D40.3 (A), D41.3 (A), R12.2, R136.2, R146.2, R149.2, U3.2 (GND), U13.2 (GND), U17.2 (GND), U18.2 (GND); also elsewhere on the board
unnamed: FL2.1, U3.7 (CANH)
unnamed: FL2.2, U3.6 (CANL)
unnamed: R11.2, U3.4 (RXD)
unnamed: R12.1, U3.8 (STB)
unnamed: R10.2, U3.1 (TXD)
unnamed: FL3.1, U13.7 (CANH)
unnamed: FL3.2, U13.6 (CANL)
unnamed: R135.2, U13.4 (RXD)
unnamed: R136.1, U13.8 (STB)
unnamed: R134.2, U13.1 (TXD)
unnamed: FL4.1, U17.7 (CANH)
unnamed: FL4.2, U17.6 (CANL)
unnamed: R145.2, U17.4 (RXD)
unnamed: R146.1, U17.8 (STB)
unnamed: R144.2, U17.1 (TXD)
unnamed: FL5.1, U18.7 (CANH)
unnamed: FL5.2, U18.6 (CANL)
unnamed: R148.2, U18.4 (RXD)
unnamed: R149.1, U18.8 (STB)
unnamed: R147.2, U18.1 (TXD)

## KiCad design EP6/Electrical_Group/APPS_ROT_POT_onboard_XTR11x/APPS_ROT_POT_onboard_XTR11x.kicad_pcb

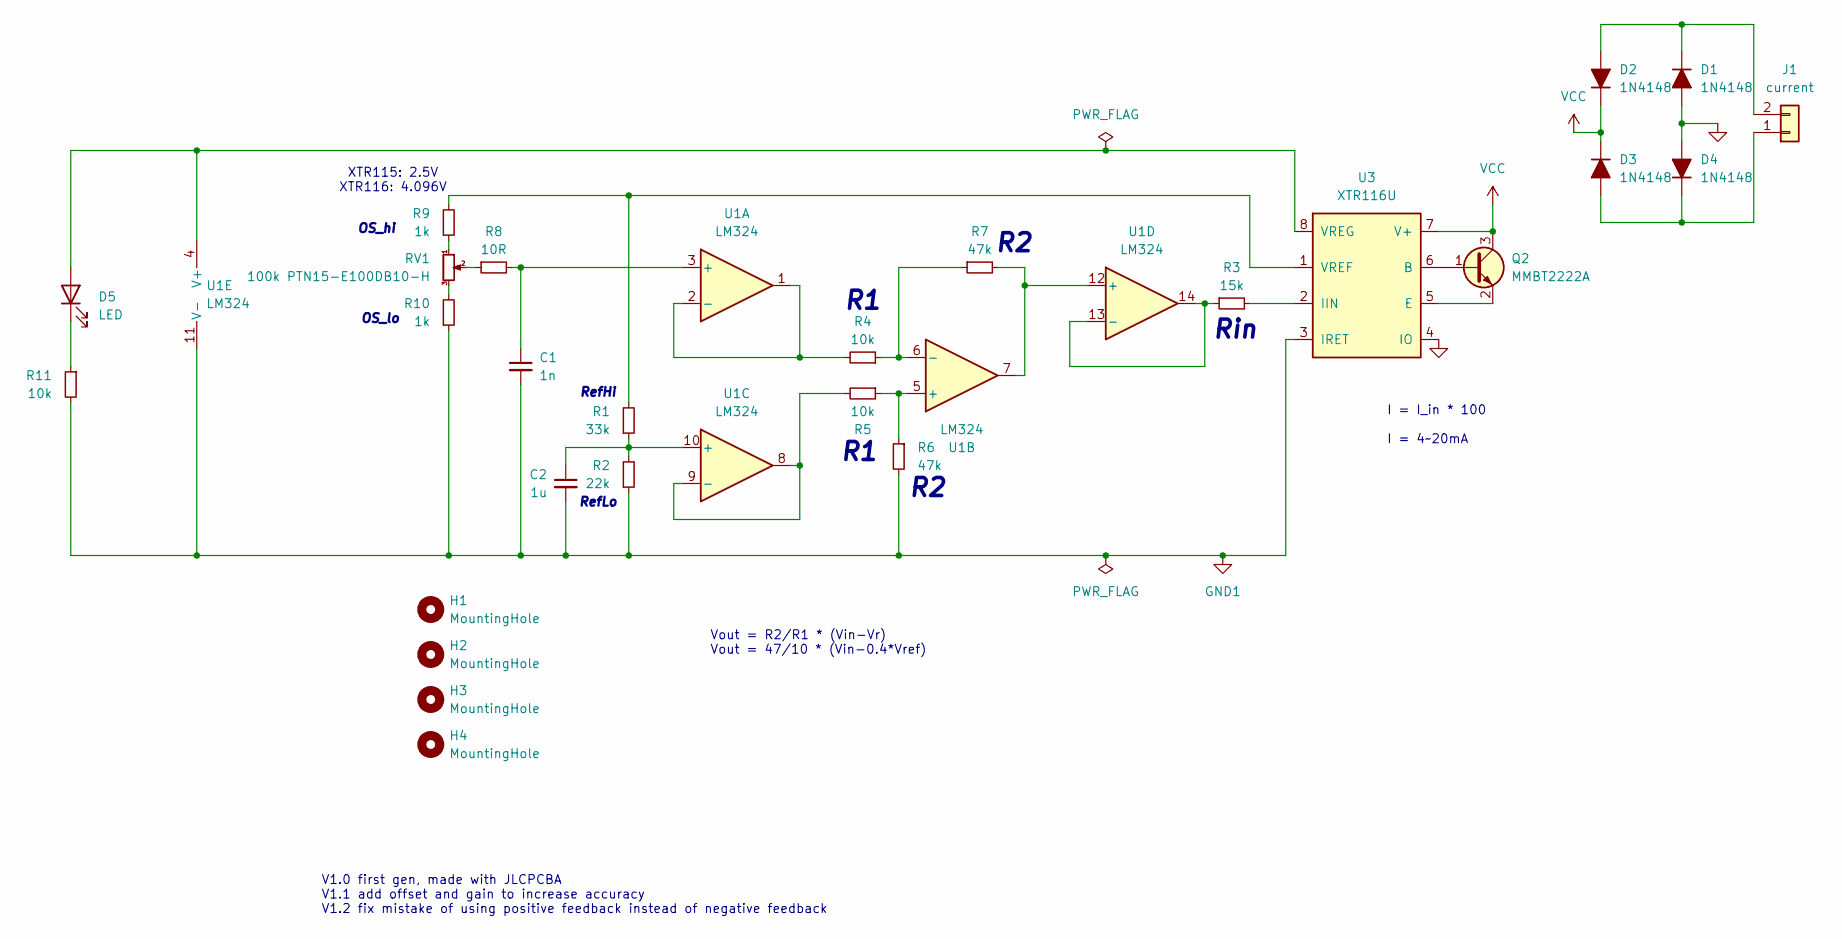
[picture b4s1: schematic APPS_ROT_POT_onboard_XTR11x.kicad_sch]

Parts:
C1: 1n; C_0402_1005Metric
C2: 1u; C_0402_1005Metric
D1, D2, D3, D4: 1N4148; D_SOD-323_HandSoldering
D5: LED; LED_0603_1608Metric
H1, H2, H3, H4: MountingHole; MountingHole_3.2mm_M3
J1: current; JST_XH_S2B-XH-A_1x02_P2.50mm_Horizontal; Part Number 1-0201FBV0T
Q2: MMBT2222A; SOT-23
R1: 33k; R_0402_1005Metric
R2: 22k; R_0402_1005Metric
R3: 15k; R_0402_1005Metric
R4, R5, R11: 10k; R_0402_1005Metric
R6, R7: 47k; R_0402_1005Metric
R8: 10R; R_0402_1005Metric
R9, R10: 1k; R_0402_1005Metric
RV1: 100k PTN15-E100DB10-H; Potentiometer_Piher_PT-15-V15_Vertical_Hole
U1: LM324; SOIC-14_3.9x8.7mm_P1.27mm
U3: XTR116U; SOIC-8_3.9x4.9mm_P1.27mm

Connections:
GND: D1.2 (A), D4.2 (A), U3.4 (IO)
GND1: C1.2, C2.2, R2.1, R6.2, R10.1, R11.2, U1.11 (V-), U3.3 (IRET)
unnamed: D1.1 (K), D2.2 (A), J1.2
unnamed: D3.2 (A), D4.1 (K), J1.1
unnamed: D5.2 (A), U1.4 (V+), U3.8 (VREG)
unnamed: D5.1 (K), R11.1
unnamed: Q2.1 (B), U3.6 (B)
unnamed: Q2.2 (E), U3.5 (E)
unnamed: R8.1, RV1.2
unnamed: R9.1, RV1.1
unnamed: R10.2, RV1.3
unnamed: C1.1, R8.2, U1.3 (+)
unnamed: R4.2, U1.1, U1.2 (-)
unnamed: R5.1, R6.1, U1.5 (+)
unnamed: R4.1, R7.1, U1.6 (-)
unnamed: C2.1, R1.1, R2.2, U1.10 (+)
unnamed: R5.2, U1.8, U1.9 (-)
unnamed: R7.2, U1.7, U1.12 (+)
unnamed: R3.1, U1.13 (-), U1.14
unnamed: R3.2, U3.2 (IIN)
unnamed: R1.2, R9.2, U3.1 (VREF)
VCC: D2.1 (K), D3.1 (K), Q2.3 (C), U3.7 (V+)

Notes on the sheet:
OS_hi
Vout = R2/R1 * (Vin-Vr) Vout = 47/10 * (Vin-0.4*Vref)
OS_lo
I = I_in * 100 I = 4~20mA
RefLo
XTR115: 2.5V XTR116: 4.096V
RefHi
V1.0 first gen, made with JLCPCBA V1.1 add offset and gain to increase accuracy V1.2 fix mistake of using positive feedback instead of negative feedback
Rin
